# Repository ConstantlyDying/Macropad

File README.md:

## NOTE:
Will make the CAD and Firmware soon:)

# Macropad

Hack Club's first wireless macropad with haptics powered by a Raspberry Pi Pico W!!
Consists of 11 Cherry MX Switches with per key RGB lighting, two EC-11 Rotary Encoders and an 0.91inch OLED Display.

I've made this as in my experience off the shelf macropads are way too expensive for the features they offer and are also very generic.
This is an alternative that is actually unique with multiple customizable switches, rotary encoders, a display, Wireless & Wired connectivity and insanely good haptics.

## Fully customizable ofc; But this is what I've planned to do:

- 9 * customizable witches for different functions.
- 2 * switches for switching between different modes/profiles of the macropad.
- 1 * rotary encoder to switch between different modes/profiles of the marcopad.
- 1 * rotary encoder for any customizable function.
- OLED Display will display the current mode, and is customizable.

# PCB

I am using JST connector footprints so that I can integrate the daughter modules to the main PCB seamlessly.

# Schematics

I am using the TP4056 module for charging the battery; MT3608 for boosting the single cell voltage; DRV2605l for accurately driving the haptics motors; Raspberry Pi Pico W for controlling everything, one more reason as to why I chose this MC is its amount of GPIO's and wireless connectivity.

# Bill Of Materials:

| SR. No: | Name:                     | Quantity: | Unit Price: (INR) | Total Price:(INR) | Unit Price: (USD) (Approx) | Total Price:(USD)(Approx) | Link:                                                                                                            |
|---------|---------------------------|-----------|-------------------|-------------------|----------------------------|---------------------------|------------------------------------------------------------------------------------------------------------------|
| 1       | Raspberry Pi Pico W       | 1         | ₹631.00           | ₹631.00           | $7.00                      | $7.00                     | https://robu.in/product/raspberry-pi-pico-w/                                                                     |
| 2       | EC11 Rotary Encoder       | 2         | ₹55.00            | ₹110.00           | $1.00                      | $2.00                     | https://robu.in/product/hongyan-ec11h-7ce20p1zy20-rotary-encoder-with-push-button-switch-vertical-plug-in-5-pin/ |
| 3       | Cherry MX Switch*35 pack  | 1         | ₹1,880.00         | ₹1,880.00         | $20.00                     | $20.00                    | https://keychron.in/product/cherry-mx-switch-set/                                                                |
| 4       | TP4056 Module             | 1         | ₹15.00            | ₹15.00            | $1.00                      | $1.00                     | https://robu.in/product/tp4056-1a-li-ion-lithium-battery-charging-module-mini-usb/                               |
| 5       | MT3608 Module             | 1         | ₹35.00            | ₹35.00            | $1.00                      | $1.00                     | https://robu.in/product/mt3608-2a-max-dc-dc-step-up-power-module-booster-power-module/                           |
| 6       | DRV2605L Module           | 1         | ₹1,200.00         | ₹1,200.00         | $13.00                     | $13.00                    | https://robu.in/product/adafruit-drv2605l-haptic-motor-controller-stemma-qt-qwiic/                               |
| 7       | OLED Display              | 1         | ₹600.00           | ₹600.00           | $7.00                      | $7.00                     | https://robu.in/product/waveshare-128x32-general-0-91inch-oled-display-module/                                   |
| 8       | SK6812 mini - e LEDS      |           | --                | --                | --                         | --                        | Sourced Locally                                                                                                  |
| 9       | Battery (3.7v)            | 1         | ₹500.00           | ₹500.00           | $6.00                      | $6.00                     | Sourced Locally                                                                                                  |
| 10      | SPDT Switch               | 1         | ₹600.00           | ₹600.00           | $7.00                      | $7.00                     | https://robu.in/product/1-month-warranty-261/                                                                    |
| 11      | JST Connectors (Assorted) | --        |                   |                   |                            |                           | Sourced Locally                                                                                                  |
| 12      | PCB Fabrication           | 1         | ₹1,700.00         | ₹1,700.00         | $17.00                     | $17.00                    | JLC PCB                                                                                                          |
|         |                           | TOTAL:    | ₹7,216.00         | ₹7,271.00         | $80.00                     | $81.00                    |                                                                                                                  |

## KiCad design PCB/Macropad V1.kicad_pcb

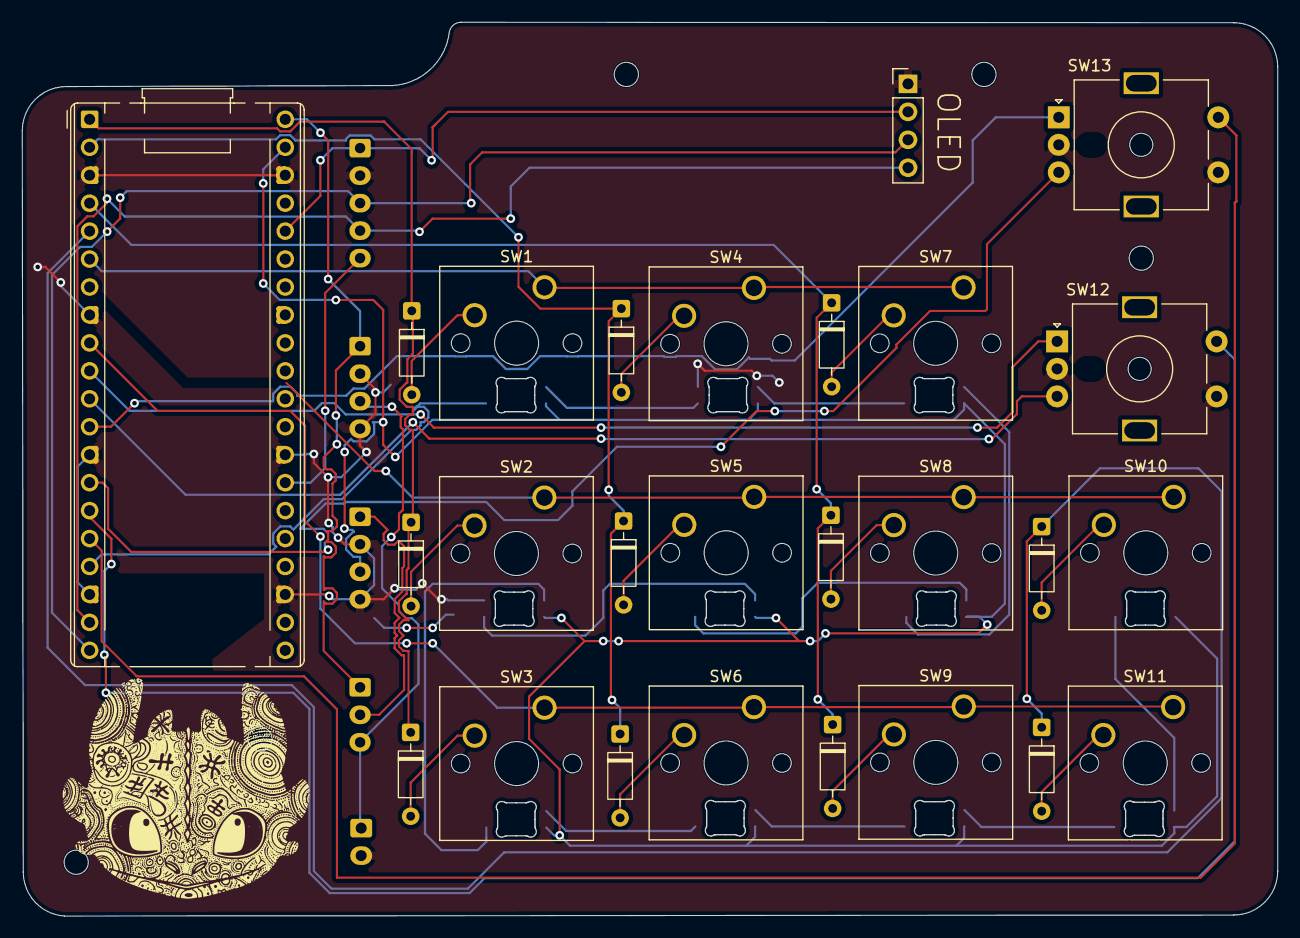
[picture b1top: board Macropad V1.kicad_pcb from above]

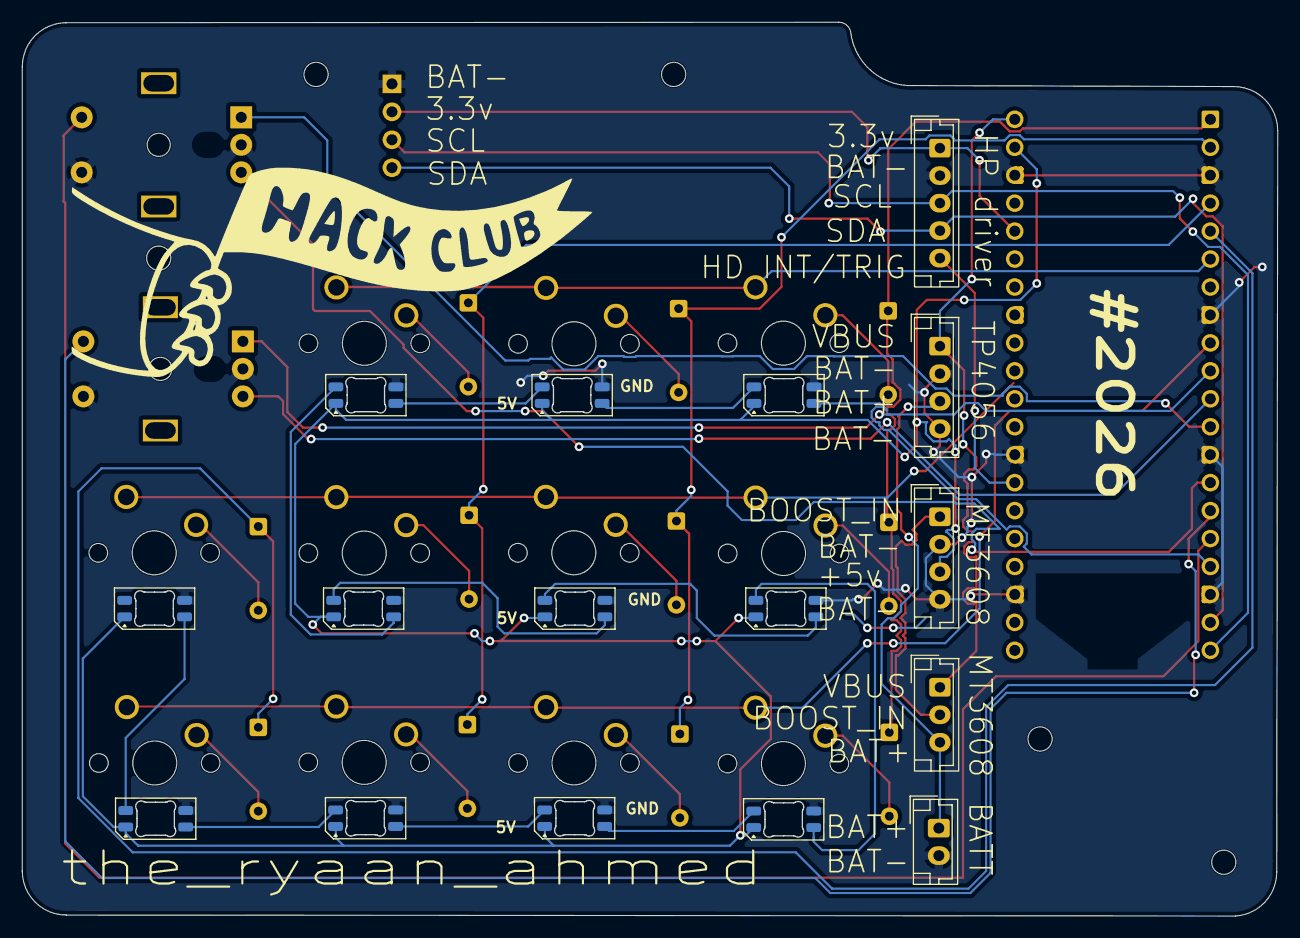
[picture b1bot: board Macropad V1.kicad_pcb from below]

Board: 2 copper layers, 114.1 x 81.2 mm, 42 parts (16 on the bottom side), 44 nets.

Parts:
A1: RaspberryPi_Pico_W; RaspberryPi_Pico_Common_THT
D10, D13, D14, D15, D16, D17, D18, D20, D21, D22, D23: SK6812MINI-E; LED_SK6812MINI-E_3.2x2.8mm_P1.5mm_ReverseMount
D34, D35, D36, D37, D38, D39, D40, D41, D42, D44, D45: 1N4148; D_DO-35_SOD27_P7.62mm_Horizontal
J1: MT3608 pins; JST_EH_B4B-EH-A_1x04_P2.50mm_Vertical
J2: TP4056 pins; JST_EH_B4B-EH-A_1x04_P2.50mm_Vertical
J3: Battery Pads; JST_EH_B2B-EH-A_1x02_P2.50mm_Vertical
J5: DRV2605l pins; JST_EH_B5B-EH-A_1x05_P2.50mm_Vertical
SW1, SW2, SW3, SW4, SW5, SW6, SW7, SW8, SW9, SW10, SW11: SW_Push_45deg; SW_Cherry_MX_1.00u_PCB
SW12, SW13: RotaryEncoder_Switch; RotaryEncoder_Alps_EC11E-Switch_Vertical_H20mm_MountingHoles
SW14: SW_SPDT; JST_EH_B3B-EH-A_1x03_P2.50mm_Vertical
U1: ER_OLEDM0.91_1x-I2C; PinHeader_1x04_P2.54mm_Vertical

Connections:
+3.3V: A1.36 (3V3), J5.1, U1.2 (VCC)
+5V: A1.39 (VSYS), D10.1 (VDD), D13.1 (VDD), D14.1 (VDD), D15.1 (VDD), D16.1 (VDD), D17.1 (VDD), D18.1 (VDD), D20.1 (VDD), D21.1 (VDD), D22.1 (VDD), D23.1 (VDD), J1.3
BAT+: J2.3, J3.1, SW14.3 (C)
BAT-: A1.3 (GND), A1.8 (GND), A1.13 (GND), A1.18 (GND), A1.23 (GND), A1.28 (GND), A1.38 (GND), D10.3 (VSS), D13.3 (VSS), D14.3 (VSS), D15.3 (VSS), D16.3 (VSS), D17.3 (VSS), D18.3 (VSS), D20.3 (VSS), D21.3 (VSS), D22.3 (VSS), D23.3 (VSS), J1.2, J1.4, J2.2, J2.4, J3.2, J5.2, SW12.C, SW12.S1, SW13.C, SW13.S1, U1.1 (GND)
BOOST_IN: J1.1, SW14.2 (B)
COL1: A1.6 (GPIO4), SW1.1, SW4.1, SW7.1
COL2: A1.7 (GPIO5), SW2.1, SW5.1, SW8.1, SW10.1
COL3: A1.9 (GPIO6), SW3.1, SW6.1, SW9.1, SW11.1
HD INT/TRIG: A1.27 (GPIO21), J5.5
LED IN: A1.17 (GPIO13), D10.4 (DIN)
unnamed: D10.2 (DOUT), D13.4 (DIN)
unnamed: D13.2 (DOUT), D14.4 (DIN)
unnamed: D14.2 (DOUT), D15.4 (DIN)
unnamed: D15.2 (DOUT), D16.4 (DIN)
unnamed: D16.2 (DOUT), D17.4 (DIN)
unnamed: D17.2 (DOUT), D18.4 (DIN)
unnamed: D18.2 (DOUT), D20.4 (DIN)
unnamed: D20.2 (DOUT), D22.4 (DIN)
unnamed: D21.4 (DIN), D22.2 (DOUT)
unnamed: D21.2 (DOUT), D23.4 (DIN)
unnamed: D34.2 (A), SW1.2
unnamed: D35.2 (A), SW2.2
unnamed: D36.2 (A), SW3.2
unnamed: D37.2 (A), SW4.2
unnamed: D38.2 (A), SW5.2
unnamed: D39.2 (A), SW6.2
unnamed: D40.2 (A), SW7.2
unnamed: D41.2 (A), SW8.2
unnamed: D42.2 (A), SW9.2
unnamed: D44.2 (A), SW10.2
unnamed: D45.2 (A), SW11.2
REA1: A1.10 (GPIO7), SW12.A
REA2: A1.12 (GPIO9), SW13.A
REB1: A1.11 (GPIO8), SW12.B
REB2: A1.14 (GPIO10), SW13.B
RES1: A1.15 (GPIO11), SW12.S2
RES2: A1.16 (GPIO12), SW13.S2
ROW1: A1.1 (GPIO0), D34.1 (K), D35.1 (K), D36.1 (K)
ROW2: A1.2 (GPIO1), D37.1 (K), D38.1 (K), D39.1 (K)
ROW3: A1.4 (GPIO2), D40.1 (K), D41.1 (K), D42.1 (K)
ROW4: A1.5 (GPIO3), D44.1 (K), D45.1 (K)
SCL: A1.20 (GPIO15), J5.3, U1.3 (SCL)
SDA: A1.19 (GPIO14), J5.4, U1.4 (SDA)
VBUS: A1.40 (VBUS), J2.1, SW14.1 (A)
